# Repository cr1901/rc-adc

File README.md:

# `rc-adc`

TODO: Document how to use/how the RC circuit should be set up. For now, here's
a pretty graph:

Alt text: Picture of two plots of time versus digital output value. A triangle
ramp wave was applied to the ADC comparator's positive terminal. The FPGA
applies a 3.3V signal an RC circuit; the comparator's negative terminal is
connected to the high side of the capacitor. The FPGA counts how many clock
cycles it takes before the voltage across the capacitor in the RC circuit
becomes more positive than the comparator's positive terminal. When this
happens, the comparator goes from outputting a 1 and starts outputting a 0. The
FPGA charges the RC circuit for a harcoded number of clock cycles that
corresponds 3.3/2 Volts. Once that voltage is reached, the FPGA discharges
the RC circuit back to 0V and the process repeats.

The time it takes for the RC circuit to charge to a specific voltage
is not linear. A LUT and multiplier created alongside the ADC converts the
raw clock cycle count to a linear digital reading from 0 to 255. The
difference in shape between the raw (blue) and corrected (yellow) plots
is apparent, with the blue plot being noticably more curved, and the yellow
plot more linear.

The comparator only activates at a voltage difference above 100mV or so. Below
100mV, both the raw and corrected plots slowly bend toward a digital reading
of 0, indicating nonlinearities. This is in contrast to the expected sudden
transition that occurs in the triangle ramp applied to the ADC comparator's
positive terminal when it reaches 0 Volts. The closer _both_ the positive and
negative terminal voltages are to 0, the less likely the comparator will
correctly detect that the positive terminal was ever above the negative
terminal at all. This in turn distorts the how many cycles the FPGA counts
before the RC circuit voltage goes above the positive terminal, and so very
low input voltages get mapped to lower counts/linear readings than they
should. AFAIK, there is not much I can do about this.

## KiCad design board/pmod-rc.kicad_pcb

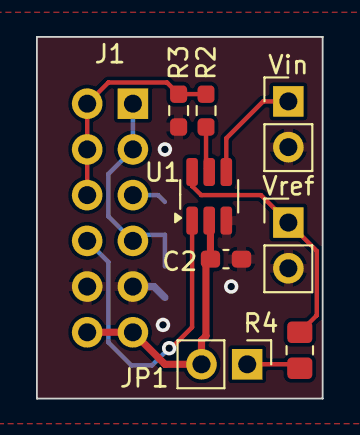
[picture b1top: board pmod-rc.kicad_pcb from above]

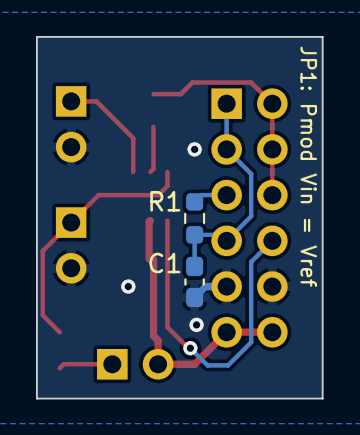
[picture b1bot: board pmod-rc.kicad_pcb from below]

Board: 2 copper layers, 15.9 x 20.1 mm, 11 parts (2 on the bottom side), 10 nets.

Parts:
C1: 1nF; C_0603_1608Metric_Pad1.08x0.95mm_HandSolder
C2: 1uF; C_0603_1608Metric_Pad1.08x0.95mm_HandSolder
J1: Pmod_SpecB
J2: Vin; PinHeader_1x02_P2.54mm_Vertical
J3: Vref; PinHeader_1x02_P2.54mm_Vertical
JP1: Jumper_2_Open; PinHeader_1x02_P2.54mm_Vertical
R1: 100k; R_0603_1608Metric_Pad0.98x0.95mm_HandSolder
R2, R3: 10k; R_0603_1608Metric_Pad0.98x0.95mm_HandSolder
R4: 33; R_0805_2012Metric_Pad1.20x1.40mm_HandSolder
U1: TMUX1119DBVR; SOT-23-6_Handsoldering

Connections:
+3.3V: C2.1, J1.6, J1.12, JP1.2 (B), U1.2 (VDD)
/CHARGE: J1.3, R1.2
/SEL: J1.10, U1.1 (SEL)
/SENSE_HI: J1.7, J1.8, J1.9, R2.1, R3.2
/SENSE_LO: C1.1, J1.1, J1.2, J1.4, R1.1
GND: C1.2, C2.2, J1.5, J1.11, J2.2, J3.2, R3.1, U1.3 (GND)
unnamed: J2.1, U1.4 (S1)
unnamed: J3.1, R4.2, U1.6 (S2)
unnamed: JP1.1 (A), R4.1
unnamed: R2.2, U1.5 (D)

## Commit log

2025-03-03 Hardcoded MVP working.
2025-03-03 Move all DAC debug outputs to LEDs, remove other LED debug signals, add a sweep module using PMOD R2R for testing.
2025-03-03 More minor cleanups.
2025-03-03 Add debug interface. Fix off-by-one error in normalization.
2025-03-03 Move module vars into parameters and __main__.
2025-03-04 Split icebreaker example into more modules.
2025-03-04 Apply lints, add sample rate property to RcAdc.
2025-03-04 Fix sweep_Hz parameter- incorrectly implemented.
2025-03-04 Add README.md placeholder.
2025-03-04 Convert project to use PDM.
2025-03-08 Check in a fully routed PMOD-RC board.
2025-03-08 Refactor ADC classes out of icebreaker example.
2025-03-08 Add failing basic test for RcAdc.
2025-03-09 Make RcAdc a Component, update test and icebreaker example.
2025-03-09 Fix off-by-one error when counting charge/discharge times.
2025-03-13 Add UART plotting to icebreaker example.
2025-03-13 Fix offset error by shifting theoretical charge time before calculating LUT entries, instead of adding a constant bias to LUT entries; removes gain error. Also, offset for ice40 is closer to .120mV, 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
2025-03-13 Use a sigmoid to smooth out measurements below thresh voltages instead of if-else.
2025-03-13 Add a correction to LUT for non-ideal comparators.
2025-03-13 Add unused code to RcAdc to examine the count signal directly.
2025-03-13 Provide a debug interface for ADC.
2025-03-14 Use Boneless CPU to control icebreaker ADC/DAC transfers.
2025-03-14 Refactor Boneless control program.
